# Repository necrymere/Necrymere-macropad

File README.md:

#  MintPad

 A 9 key macropad with a rotary encoder, backlight and OLED display. It uses KMK firmware.

 I made it mostly because I am a multitasker and I think it will help me. Also made it really modular cause I do a lot of things and I love flexibility.

 ## Features:

 - Blank case with an engraving on the backside to leave space for me to decorate the rest however I feel like in the moment.
 - OLED display for showing what mode it is in/silly things that I have yet to think about
 - EC11 Rotary encoder for volume control(and once pressed for changing the modes)
 - 9 LEDs, one for each key to let me customise the colour of it based on my vibe(curently my setup is mint green so I programed it that way)
 - 9 keys
 - 4 modes at the moment of writing this(probably will add more and hopefully adjust this count too)

 ## CAD Model:
 Everything should fit with screws(not sure what size but I will figure it out when I get it and go to the hardware store to buy some) or I will just glue the two parts but it is not the best option.

 The case sits at an angle which was very important to me. I hope it does not mess anything up as I spent a lot on it.

 Made in Tinkercad(which I will hopefully not touch with a 10 meter pole for a while) cause my laptop decided that Fusion360 isn't necesarry and I am demanding too much.

 Link to the Tinkercad model:https://www.tinkercad.com/things/kG7QE5OvPvF-fabulous-blorr-jofo
 ## Schematic:
 This is the schematic which didn't come with too may issues unlike last time I tried(and failed) to build for Hackpad.

## PCB:
With the PCB the issue was spacing the keycaps mostly and almost getting the direction of the OLED wrong but the rest was fine honestly(again way better than last time).

NOTE: Just noticed the OLED is wrong in this image too. I will change it when I can.

## Frimware overview:
It uses KMK for everything.

It has a rotary encoder that controls the volume and mode as stated before, 9 keys with shortcuts depending on the mode and an OLED for showing the current mode which I will have to spice up ASAP.

## BOM:
List of parts:

- Seeed Studio XIAO Microcontroller
- 0.91" 128x32 I2C OLED Display (SSD1306)
- EC11 Rotary Encoder with Push Button
- Mechanical Key Switches (x9)
- 1U Keycaps (x9)
- Custom PCB
- 3D Printed case
- 1N4148 Signal Diodes (x10)
- LEDs (x10)

## Extra stuff:
I just had a heart attack cause my firmware was from one year ago, all of it but luckly I think I found the right one. Fingers crossed.
This was really fun(excluding the loosing the firmare at midnight part) anyways hope you have a great day/evening/night!

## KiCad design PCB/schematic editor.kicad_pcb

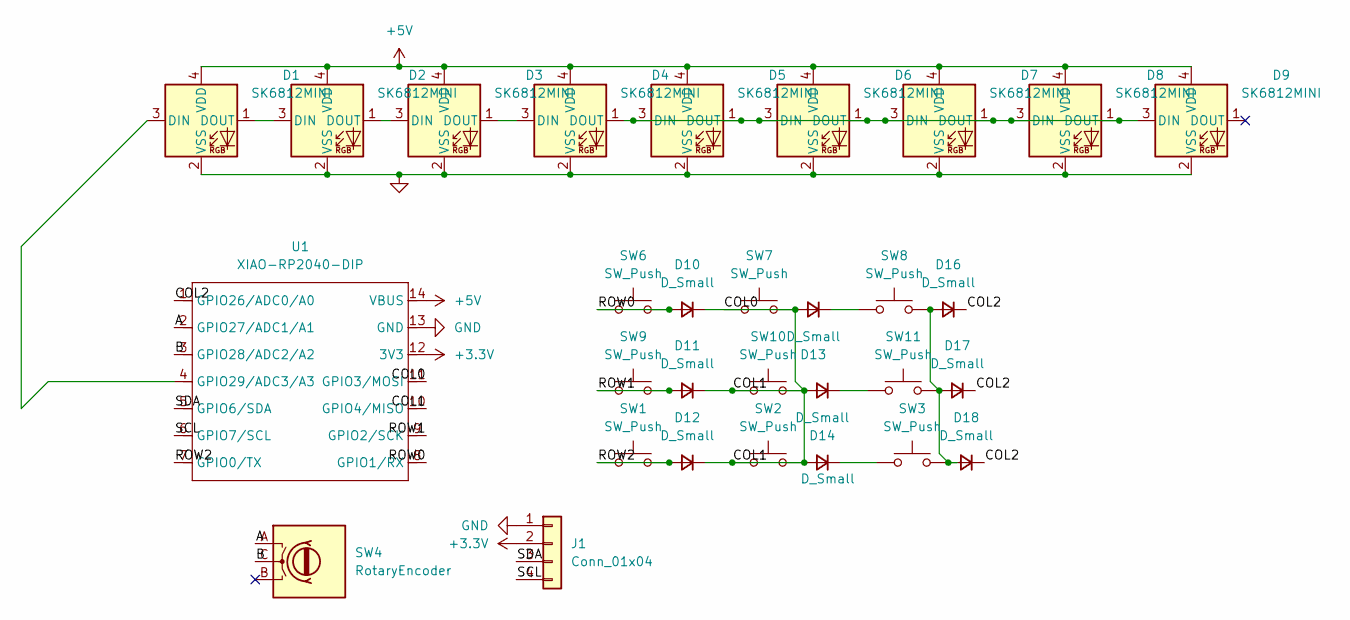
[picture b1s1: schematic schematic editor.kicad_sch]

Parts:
D1, D2, D3, D4, D5, D6, D7, D8, D9: SK6812MINI; LED_SK6812MINI_PLCC4_3.5x3.5mm_P1.75mm
D10, D11, D12, D13, D14, D15, D16, D17, D18: D_Small; D_DO-35_SOD27_P7.62mm_Horizontal
J1: Conn_01x04; PinHeader_1x04_P2.54mm_Vertical
SW1, SW2, SW3, SW6, SW7, SW8, SW9, SW10, SW11: SW_Push; SW_Cherry_MX_1.00u_PCB
SW4: RotaryEncoder; RotaryEncoder_Alps_EC11E_Vertical_H20mm
U1: XIAO-RP2040-DIP; DIP-14_W7.62mm

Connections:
+3.3V: J1.2, U1.12 (3V3)
+5V: D1.4 (VDD), D2.4 (VDD), D3.4 (VDD), D4.4 (VDD), D5.4 (VDD), D6.4 (VDD), D7.4 (VDD), D8.4 (VDD), D9.4 (VDD), U1.14 (VBUS)
/A: SW4.A, U1.2 (GPIO27/ADC1/A1)
/B: SW4.C, U1.3 (GPIO28/ADC2/A2)
/COL2: D16.1 (K), D17.1 (K), D18.1 (K), U1.1 (GPIO26/ADC0/A0)
/ROW0: D10.2 (A), SW6.1, SW6.2, U1.8 (GPIO1/RX)
/ROW1: D11.2 (A), SW9.1, SW9.2, U1.9 (GPIO2/SCK)
/ROW2: D12.2 (A), SW1.1, SW1.2, U1.7 (GPIO0/TX)
/SCL: J1.4, U1.6 (GPIO7/SCL)
/SDA: J1.3, U1.5 (GPIO6/SDA)
GND: D1.2 (VSS), D2.2 (VSS), D3.2 (VSS), D4.2 (VSS), D5.2 (VSS), D6.2 (VSS), D7.2 (VSS), D8.2 (VSS), D9.2 (VSS), J1.1, U1.13 (GND)
unnamed: D1.3 (DIN), U1.4 (GPIO29/ADC3/A3)
unnamed: D1.1 (DOUT), D2.3 (DIN)
unnamed: D2.1 (DOUT), D3.3 (DIN)
unnamed: D3.1 (DOUT), D4.3 (DIN)
unnamed: D4.1 (DOUT), D5.1 (DOUT), D5.3 (DIN), D6.1 (DOUT), D6.3 (DIN), D7.1 (DOUT), D7.3 (DIN), D8.1 (DOUT), D8.3 (DIN), D9.3 (DIN)
unnamed: D13.1 (K), SW8.1
unnamed: D14.1 (K), SW11.1
unnamed: D15.1 (K), SW3.1
unnamed: D16.2 (A), D17.2 (A), D18.2 (A), SW3.2, SW8.2, SW11.2

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
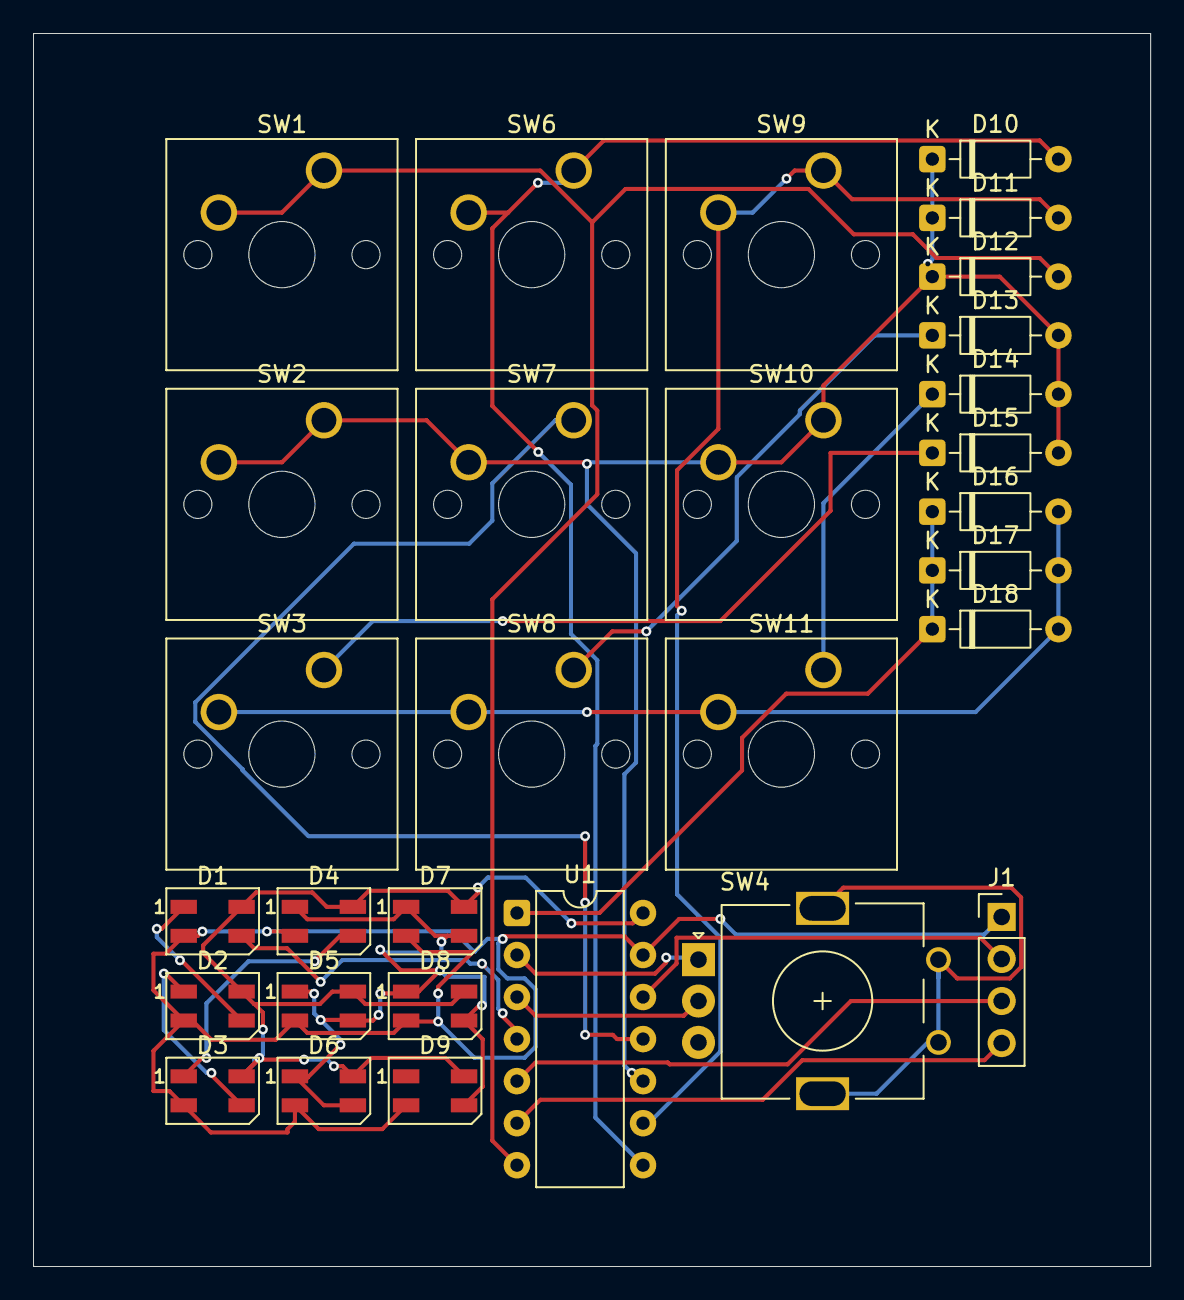
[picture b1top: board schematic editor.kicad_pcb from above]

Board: 2 copper layers, 67.5 x 74.5 mm, 30 parts (0 on the bottom side), 22 nets.

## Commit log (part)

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2026-03-31 /CAD
